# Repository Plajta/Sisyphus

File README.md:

# Sisyphus
This repository includes the hardware, firmware, chassis and documentation for our soundboard helping those who need it (or don't and want a thing that makes sounds).

Code for the firmware's web configurator (Lithos) can be found [here](https://github.com/Plajta/lithos).

## Key features
Built using open source software on widely documented hardware.

With RP2040 as it's beating heart and a nice crisp I2S DAC, it can (but probably won't be used to) do CD quality audio.

Built into a strudy, but slim and relatively lite 3D printed construction, held together by friction and screws for ease of repair and construction. (construction manual coming soon™)

## Directory structure
- [3D](3D/) - FreeCAD project, the [STLs](3D/STLs) subdirectory includes the exported files ready for 3D printing
- [PCBs](PCBs/) - Two KiCAD projects, one for Sisyphus's [mainboard](PCBs/sisyphus) and one for our own slim [RGB sensor module](PCBs/rgb_sensor)
- [src](src/) - The board's firmware, has it's own README, also usable on a Raspberry Pi Pico with a bit of configuration

## Licensing
All main directories have their own LICENSE files.

`3D` and `PCBs` are under CC-BY-SA. `src` is licensed under GPL3.
That means you can use the whole thing, or just a part of it in your commercial projects but must publically share your potential changes under the same license.

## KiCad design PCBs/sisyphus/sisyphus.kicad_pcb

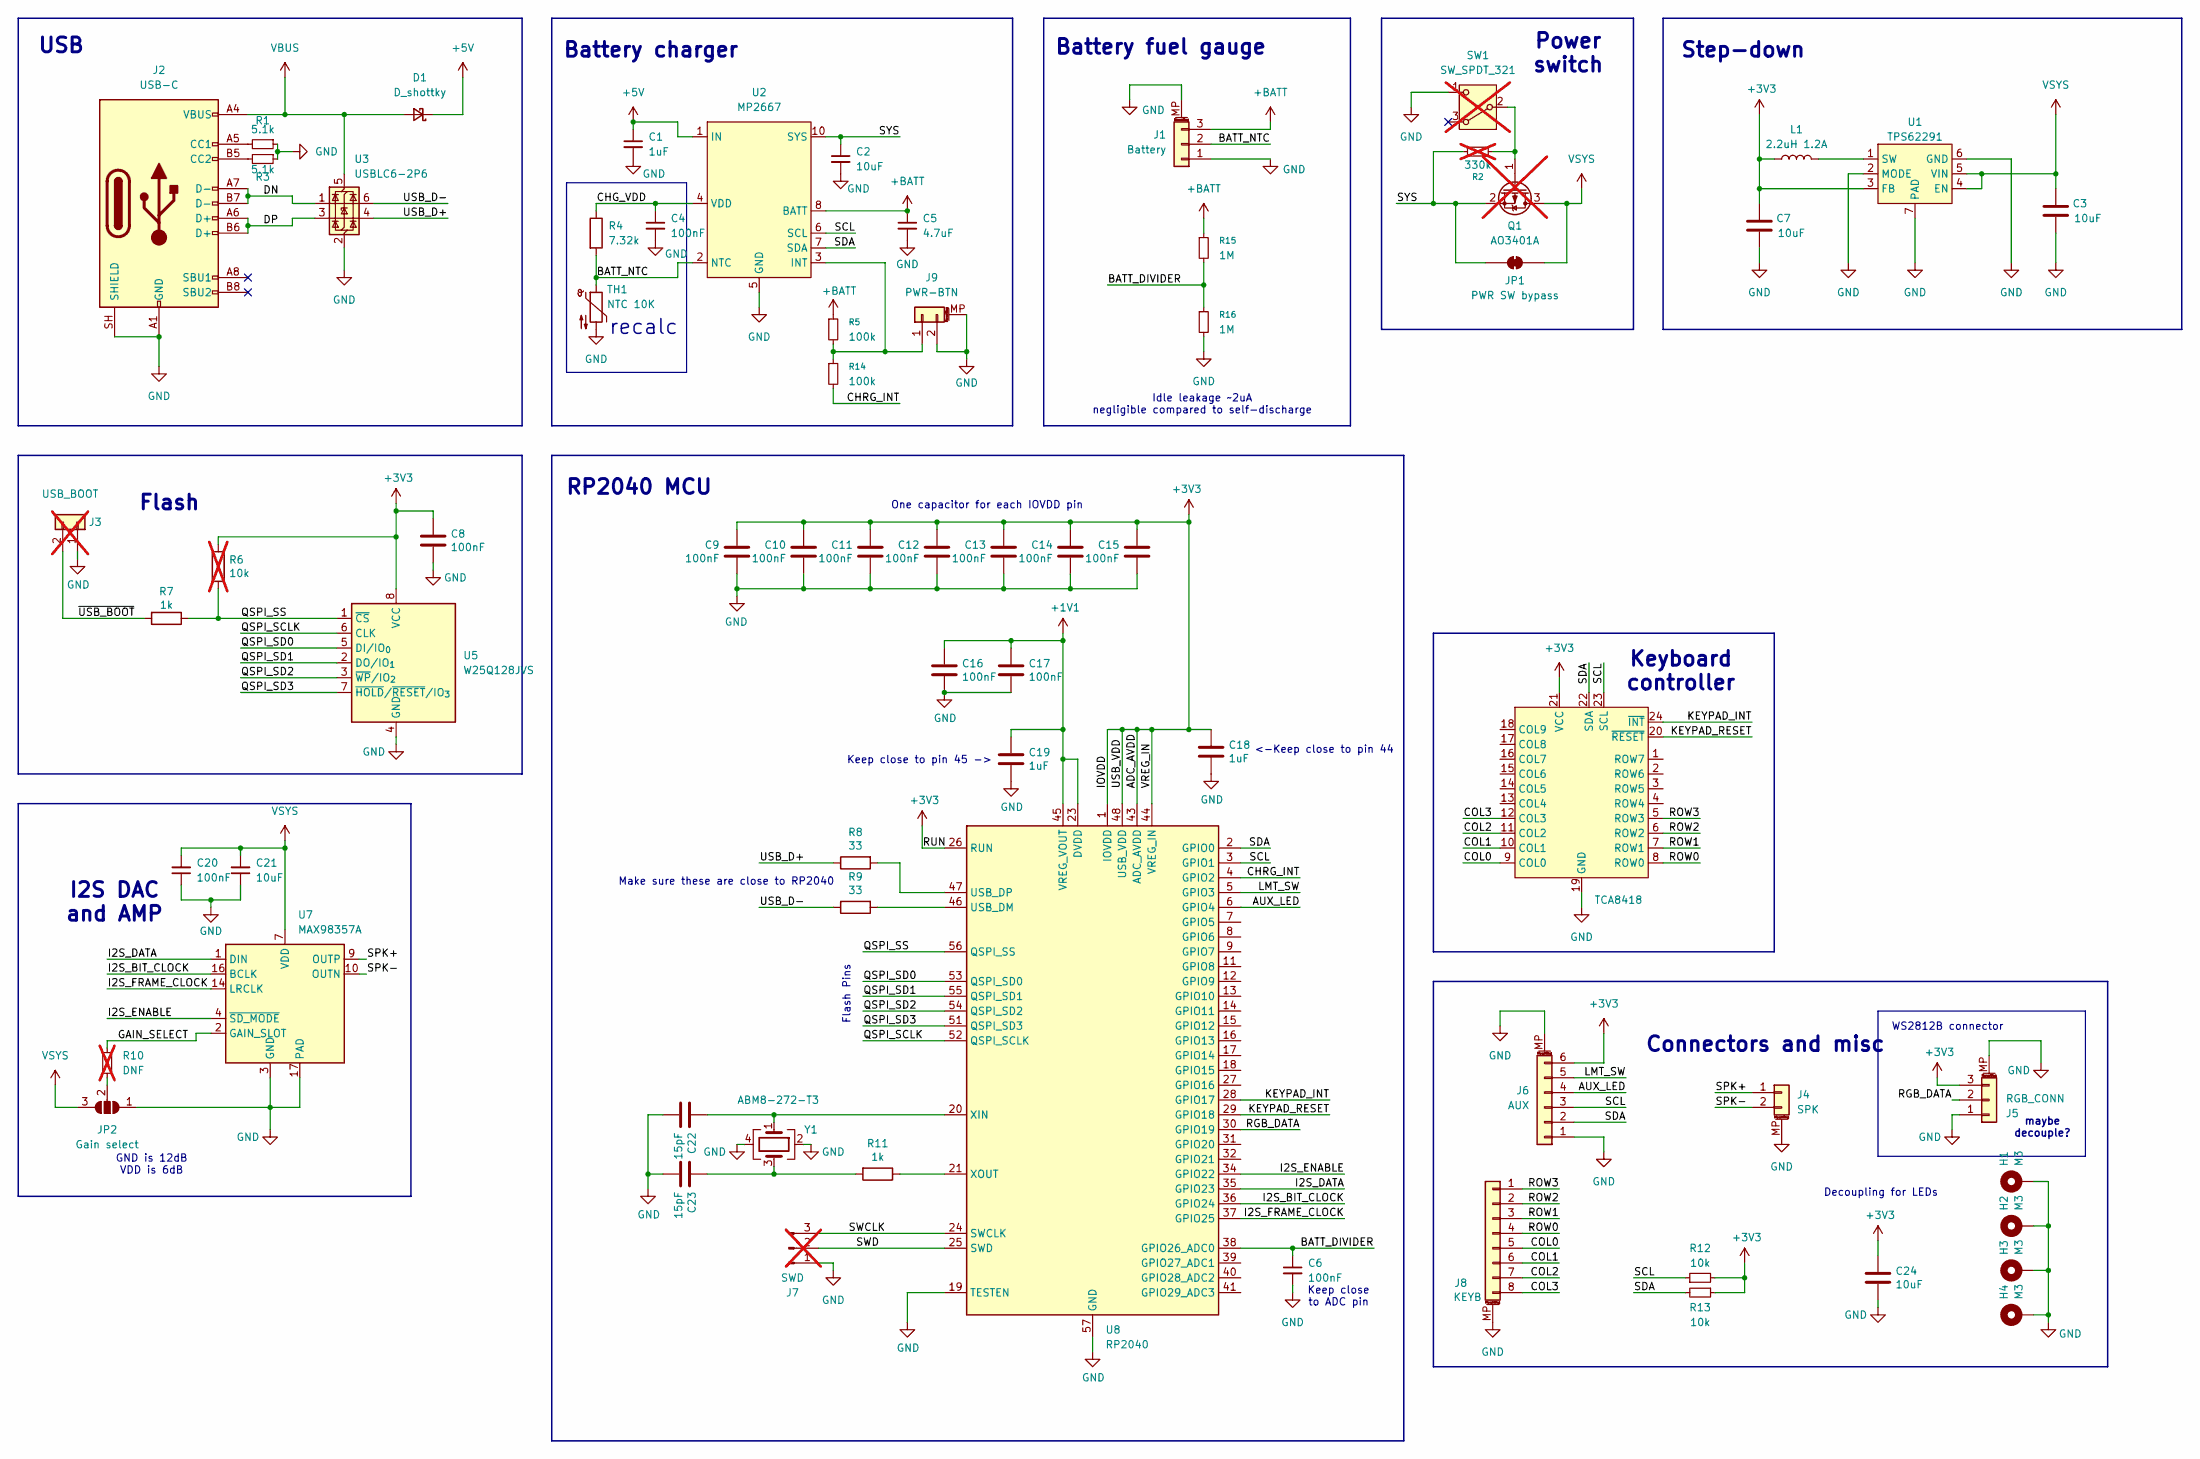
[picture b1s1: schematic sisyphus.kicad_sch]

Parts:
C1, C18, C19: 1uF; C_0402_1005Metric
C2, C3, C7, C21, C24: 10uF; C_0402_1005Metric
C4, C6, C8, C9, C10, C11, C12, C13, C14, C15, C16, C17, C20: 100nF; C_0402_1005Metric
C5: 4.7uF; C_0402_1005Metric
C22, C23: 15pF; C_0402_1005Metric
D1: D_shottky; D_SOD-123F; Mouser Part 863-MBR230LSFT1G
H1, H2, H3, H4: M3; MountingHole_3.2mm_M3_ISO7380_Pad
J1: Battery; JST_PH_S3B-PH-SM4-TB_1x03-1MP_P2.00mm_Horizontal; Mouser Part 306-S3BPHSM4TBLFSN
J2: USB-C; USB_C_Receptacle_GCT_USB4105-xx-A_16P_TopMnt_Horizontal; Mouser Part 640-USB4105-GF-A-120
J3: USB_BOOT; PinHeader_1x02_P1.00mm_Vertical; not fitted
J4: SPK; JST_PH_S2B-PH-SM4-TB_1x02-1MP_P2.00mm_Horizontal; Mouser Part 306-S2BPHSM4TBLFSN
J5: RGB_CONN; JST_PH_S3B-PH-SM4-TB_1x03-1MP_P2.00mm_Horizontal; Mouser Part 306-S3BPHSM4TBLFSN
J6: AUX; JST_PH_S6B-PH-SM4-TB_1x06-1MP_P2.00mm_Horizontal; Mouser Part 306-S6BPHSM4TBLFSN
J7: SWD; PinHeader_1x03_P2.54mm_Vertical; not fitted
J8: KEYB; JST_PH_S8B-PH-SM4-TB_1x08-1MP_P2.00mm_Horizontal; Mouser Part 306-S8BPHSM4TBLFSN
J9: PWR-BTN; JST_PH_S2B-PH-SM4-TB_1x02-1MP_P2.00mm_Horizontal; Mouser Part 306-S2BPHSM4TBLFSN
JP1: PWR SW bypass; SolderJumper-2_P1.3mm_Bridged2Bar_RoundedPad1.0x1.5mm
JP2: Gain select; SolderJumper-3_P1.3mm_Open_RoundedPad1.0x1.5mm
L1: 2.2uH 1.2A; L_0805_2012Metric
Q1: AO3401A; SOT-23; LCSC Part C347476; not fitted
R1, R3: 5.1k; R_0402_1005Metric
R2: 330k; R_0402_1005Metric; not fitted
R4: 7.32k; R_0402_1005Metric
R5, R14: 100k; R_0402_1005Metric
R6: 10k; R_0402_1005Metric; not fitted
R7, R11: 1k; R_0402_1005Metric
R8, R9: 33; R_0402_1005Metric
R10: DNF; R_0402_1005Metric; not fitted
R12, R13: 10k; R_0402_1005Metric
R15, R16: 1M; R_0402_1005Metric
SW1: SW_SPDT_321; PinHeader_1x03_P2.54mm_Vertical; not fitted
TH1: NTC 10K
U1: TPS62291; WSON-6-1EP_2x2mm_P0.65mm_EP1x1.6mm_ThermalVias; Mouser Part 595-TPS62291DRVR
U2: MP2667; MPS_MP2664_QFN-10_2x2mm_P0.5mm; Mouser Part 946-MP2667GG-0000-P
U3: USBLC6-2P6; SOT-666; Mouser Part 511-USBLC6-2P6
U5: W25Q128JVS; SOIC-8_5.3x5.3mm_P1.27mm
U6: TCA8418; WQFN-24-1EP_4x4mm_P0.5mm_EP2.45x2.45mm; Mouser Part 595-TCA8418RTWR
U7: MAX98357A; TQFN-16-1EP_3x3mm_P0.5mm_EP1.23x1.23mm; Mouser Part 700-MAX98357AETE+T
U8: RP2040; QFN-56-1EP_7x7mm_P0.4mm_EP3.2x3.2mm; Mouser Part 358-SC091413
Y1: ABM8-272-T3; Crystal_SMD_3225-4Pin_3.2x2.5mm; Mouser Part 815-ABM8-272-T3

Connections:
+1V1: C16.1, C17.1, C19.1, U8.23 (DVDD), U8.45 (VREG_VOUT), U8.50 (DVDD)
+3V3: C7.1, C8.1, C9.1, C10.1, C11.1, C12.1, C13.1, C14.1, C15.1, C18.1, C24.1, J5.3, J6.6, L1.1, R6.1, R12.2, R13.1, U1.3 (FB), U5.8 (VCC), U6.21 (VCC), U8.1 (IOVDD), U8.10 (IOVDD), U8.22 (IOVDD), U8.26 (RUN), U8.33 (IOVDD), U8.42 (IOVDD), U8.43 (ADC_AVDD), U8.44 (VREG_IN), U8.48 (USB_VDD), U8.49 (IOVDD)
+5V: C1.1, D1.1 (K), U2.1 (IN)
+BATT: C5.1, J1.3, R5.1, R15.1, U2.8 (BATT), U2.9 (BATT)
/AUX_LED: J6.4, U8.6 (GPIO4)
/BATT_DIVIDER: C6.1, R15.2, R16.1, U8.38 (GPIO26_ADC0)
/BATT_NTC: J1.2, R4.2, TH1.1, U2.2 (NTC)
/CHG_VDD: C4.1, R4.1, U2.4 (VDD)
/CHRG_INT: R14.2, U8.4 (GPIO2)
/COL0: J8.5, U6.9 (COL0)
/COL1: J8.6, U6.10 (COL1)
/COL2: J8.7, U6.11 (COL2)
/COL3: J8.8, U6.12 (COL3)
/DN: J2.A7 (D-), J2.B7 (D-), U3.1 (I/O1)
/DP: J2.A6 (D+), J2.B6 (D+), U3.3 (I/O2)
/GAIN_SELECT: R10.1, U7.2 (GAIN_SLOT)
/I2S_BIT_CLOCK: U7.16 (BCLK), U8.36 (GPIO24)
/I2S_DATA: U7.1 (DIN), U8.35 (GPIO23)
/I2S_ENABLE: U7.4 (~SD_MODE), U8.34 (GPIO22)
/I2S_FRAME_CLOCK: U7.14 (LRCLK), U8.37 (GPIO25)
/KEYPAD_INT: U6.24 (~INT), U8.28 (GPIO17)
/KEYPAD_RESET: U6.20 (~RESET), U8.29 (GPIO18)
/LMT_SW: J6.5, U8.5 (GPIO3)
/QSPI_SCLK: U5.6 (CLK), U8.52 (QSPI_SCLK)
/QSPI_SD0: U5.5 (DI/IO_{0}), U8.53 (QSPI_SD0)
/QSPI_SD1: U5.2 (DO/IO_{1}), U8.55 (QSPI_SD1)
/QSPI_SD2: U5.3 (~WP/IO_{2}), U8.54 (QSPI_SD2)
/QSPI_SD3: U5.7 (~HOLD/~RESET/IO_{3}), U8.51 (QSPI_SD3)
/QSPI_SS: R6.2, R7.1, U5.1 (~CS), U8.56 (QSPI_SS)
/RGB_DATA: J5.2, U8.30 (GPIO19)
/ROW0: J8.4, U6.8 (ROW0)
/ROW1: J8.3, U6.7 (ROW1)
/ROW2: J8.2, U6.6 (ROW2)
/ROW3: J8.1, U6.5 (ROW3)
/SCL: J6.3, R12.1, U2.6 (SCL), U6.23 (SCL), U8.3 (GPIO1)
/SDA: J6.2, R13.2, U2.7 (SDA), U6.22 (SDA), U8.2 (GPIO0)
/SPK+: J4.1, U7.9 (OUTP)
/SPK-: J4.2, U7.10 (OUTN)
/SWCLK: J7.3, U8.24 (SWCLK)
/SWD: J7.2, U8.25 (SWD)
/SYS: C2.1, JP1.2 (B), Q1.2 (S), R2.2, U2.10 (SYS)
/USB_D+: R8.1, U3.4 (I/O2)
/USB_D-: R9.1, U3.6 (I/O1)
/~USB_BOOT: J3.2, R7.2
GND: C1.2, C2.2, C3.2, C4.2, C5.2, C6.2, C7.2, C8.2, C9.2, C10.2, C11.2, C12.2, C13.2, C14.2, C15.2, C16.2, C17.2, C18.2, C19.2, C20.1, C21.1, C22.2, C23.2, C24.2, H1.1 (1_1), H2.1 (1_1), H3.1 (1_1), H4.1 (1_1), J1.1, J1.MP (MountPin), J2.A1 (GND), J2.A12 (GND), J2.B1 (GND), J2.B12 (GND), J2.SH (SHIELD), J3.1, J4.MP (MountPin), J5.1, J5.MP (MountPin), J6.1, J6.MP (MountPin), J7.1, J8.MP (MountPin), J9.2, J9.MP (MountPin), JP2.1 (A), R1.1, R3.1, R16.2, SW1.1 (C), TH1.2, U1.2 (MODE), U1.6 (GND), U1.7 (PAD), U2.5 (GND), U3.2 (GND), U5.4 (GND), U6.19 (GND), U6.25 (PAD), U7.3 (GND), U7.11 (GND), U7.15 (GND), U7.17 (PAD), U8.19 (TESTEN), U8.57 (GND), Y1.2, Y1.4
unnamed: C23.1, R11.2, Y1.3
unnamed: J2.A5 (CC1), R1.2
unnamed: J2.B5 (CC2), R3.2
unnamed: J9.1, R5.2, R14.1, U2.3 (INT)
unnamed: JP2.2 (C), R10.2
unnamed: Q1.1 (G), R2.1, SW1.2 (B)
unnamed: L1.2, U1.1 (SW)
unnamed: R9.2, U8.46 (USB_DM)
unnamed: R8.2, U8.47 (USB_DP)
unnamed: C22.1, U8.20 (XIN), Y1.1
unnamed: R11.1, U8.21 (XOUT)
VBUS: D1.2 (A), J2.A4 (VBUS), J2.A9 (VBUS), J2.B4 (VBUS), J2.B9 (VBUS), U3.5 (VBUS)
VSYS: C3.1, C20.2, C21.2, JP1.1 (A), JP2.3 (B), Q1.3 (D), U1.4 (EN), U1.5 (VIN), U7.7 (VDD), U7.8 (VDD)

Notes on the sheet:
Keep close to ADC pin
recalc
maybe decouple?
RP2040 MCU
USB
Battery charger
Keep close to pin 45 ->
GND is 12dB VDD is 6dB
I2S DAC and AMP
WS2812B connector
Keyboard controller
Decoupling for LEDs
Flash
Make sure these are close to RP2040
One capacitor for each IOVDD pin
Power switch
<-Keep close to pin 44
Flash Pins
Connectors and misc
Idle leakage ~2uA negligible compared to self-discharge
Step-down
Battery fuel gauge

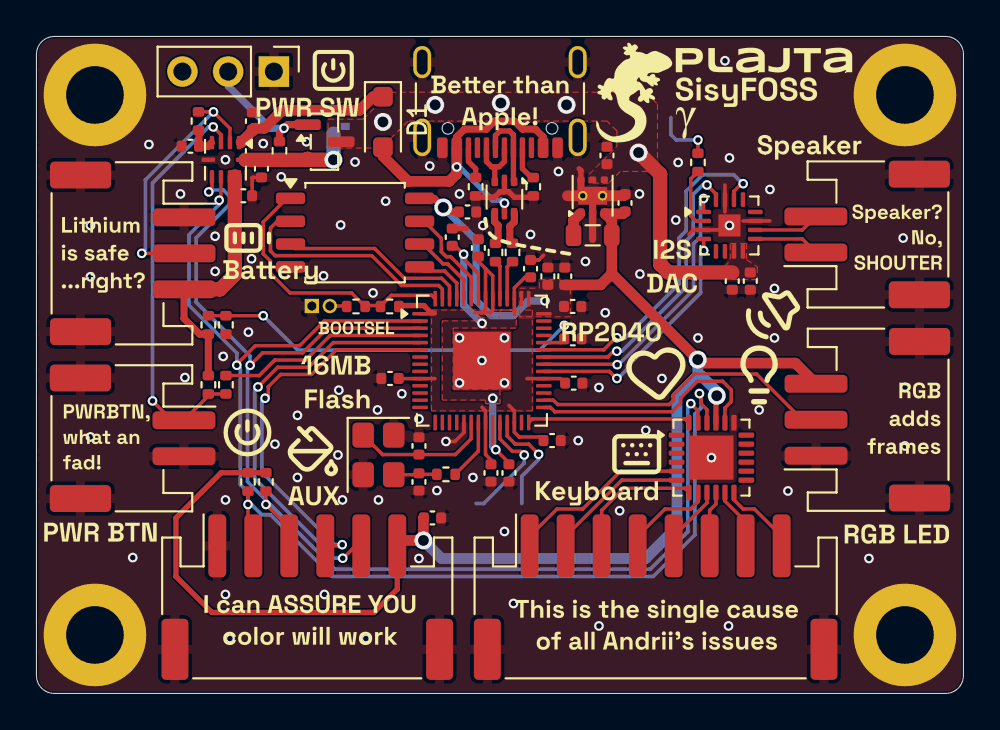
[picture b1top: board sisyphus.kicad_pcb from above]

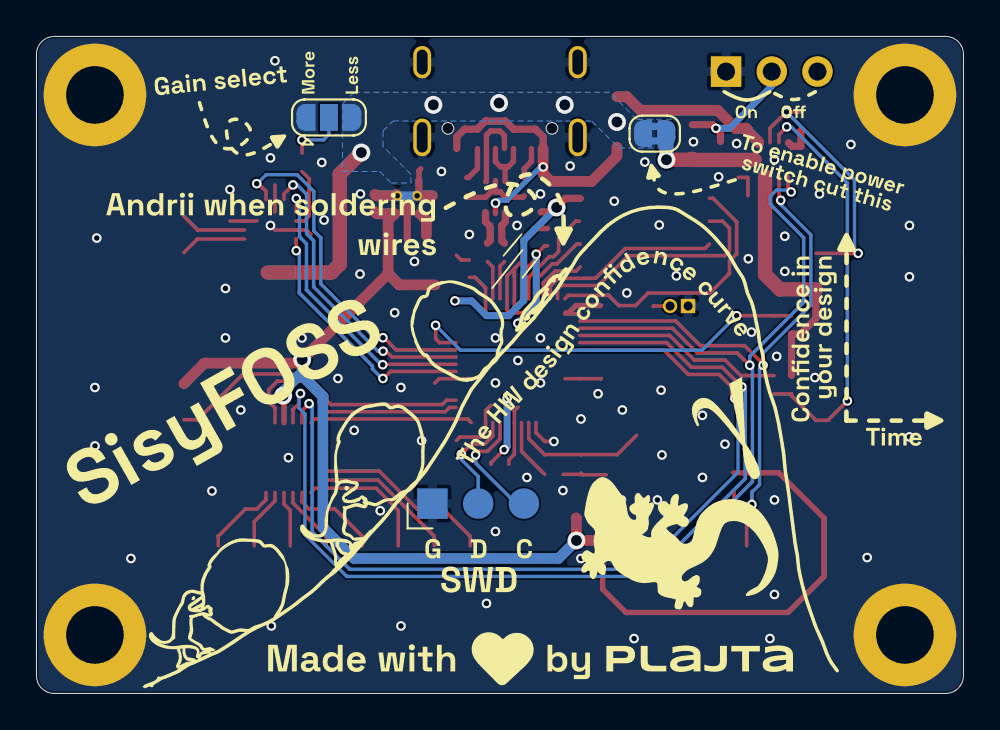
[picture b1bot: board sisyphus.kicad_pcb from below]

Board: 2 copper layers, 51.5 x 36.5 mm, 67 parts (3 on the bottom side), 58 nets.

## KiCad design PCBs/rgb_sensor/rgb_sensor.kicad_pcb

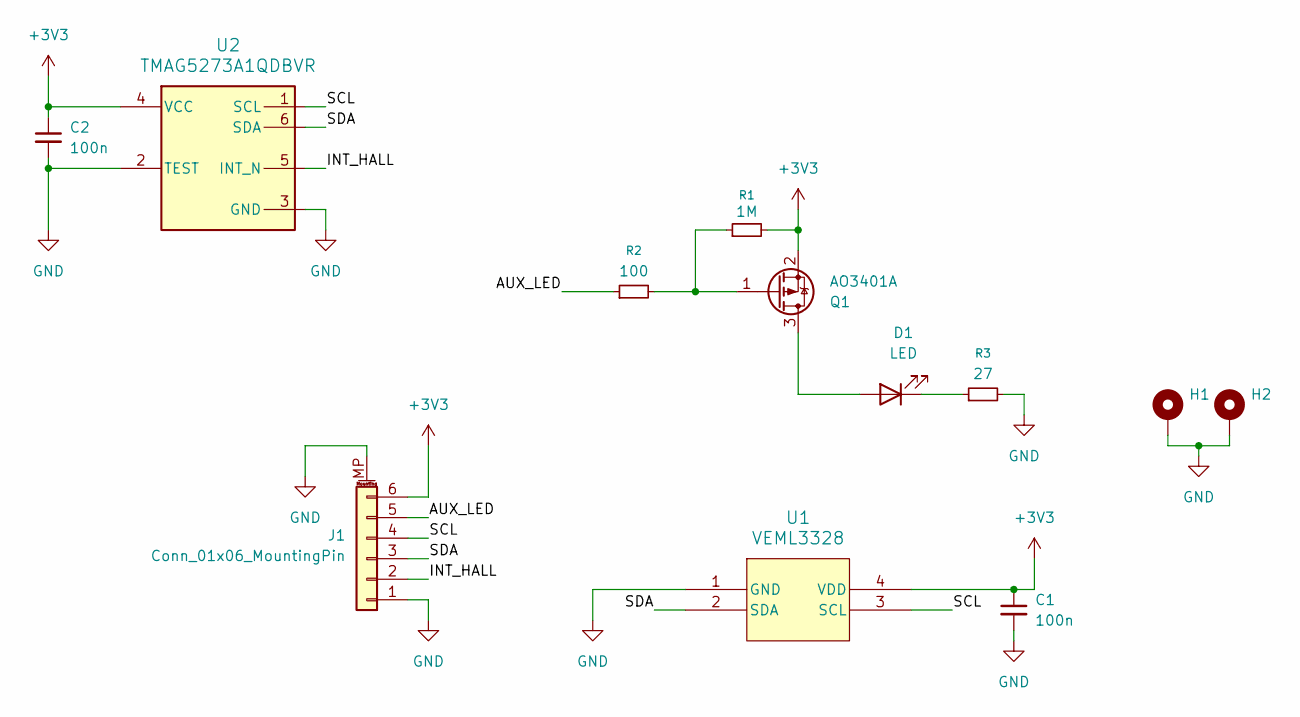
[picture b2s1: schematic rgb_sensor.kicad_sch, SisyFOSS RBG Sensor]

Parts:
C1, C2: 100n; C_0402_1005Metric
D1: LED; LED_0805_2012Metric
H1, H2: MountingHole_Pad; MountingHole_2.2mm_M2_Pad
J1: Conn_01x06_MountingPin; JST_SH_SM06B-SRSS-TB_1x06-1MP_P1.00mm_Horizontal
Q1: AO3401A; SOT-23
R1: 1M; R_0402_1005Metric
R2: 100; R_0402_1005Metric
R3: 27; R_0402_1005Metric
U1: VEML3328; SMD_L3328_VIS; Mouser Part 78-VEML3328; LCSC Part C509073
U2: TMAG5273A1QDBVR; DBV0006A-MFG; Mouser Part 595-TMAG5273A1QDBVR; LCSC Part C3716049

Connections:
+3V3: C1.1, C2.1, J1.6, Q1.2 (S), R1.2, U1.4 (VDD), U2.4 (VCC)
/AUX_LED: J1.5, R2.1
/INT_HALL: J1.2, U2.5 (INT_N)
/SCL: J1.4, U1.3 (SCL), U2.1 (SCL)
/SDA: J1.3, U1.2 (SDA), U2.6 (SDA)
GND: C1.2, C2.2, H1.1 (1_1), H2.1 (1_1), J1.1, J1.MP (MountPin), R3.2, U1.1 (GND), U2.2 (TEST), U2.3 (GND)
unnamed: D1.2 (A), Q1.3 (D)
unnamed: D1.1 (K), R3.1
unnamed: Q1.1 (G), R1.1, R2.2

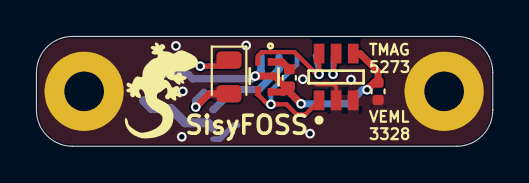
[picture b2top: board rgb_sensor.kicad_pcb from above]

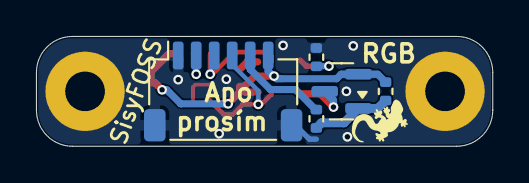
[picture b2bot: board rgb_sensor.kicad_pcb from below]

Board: 2 copper layers, 25.3 x 6.1 mm, 12 parts (5 on the bottom side), 9 nets.

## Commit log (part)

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2025-03-14 ahh piko
2025-03-14 web jede brrr
2025-03-14 velice official dashboard route
2025-03-14 uploaded modified APDS9960 code that is not working (plis helb)
2025-03-15 upravenej hlavni layout
2025-03-15 stranka na konfiguraci
2025-03-15 zobrazovat breadcrmb dynamicky pres navitem
2025-03-15 highlight veci v menu
2025-03-15 zakladni layout tlacitek
    zatim rohliky
2025-03-15 zobrazovat cursor pointer kdyz tlacitko
2025-03-15 velice scuffed modal system
2025-03-15 voice recorder
2025-03-15 shell dialogu na upravu tlacitka
2025-03-15 databaze databazuje
2025-03-15 zaklad pro handlovani souboru
2025-03-15 formwrapper a nejaky edit funkcionality
2025-03-15 nacitat tlacitka z db
2025-03-15 upravujeme nazvy tlacitek hezkym zpusobem
2025-03-15 WE CAN FINALLY SENS DA FOCKIN COLEURS
2025-03-15 nahravani obrazku a spravna velikost tlacitek
2025-03-15 responzivni uz je
2025-03-15 preahravani videa v kartach pro tlacitka
2025-03-15 podpora sheetu
2025-03-15 brat png jenom
2025-03-15 dialog funguje i s sheetem
2025-03-15 spravne brat a zobaovar breadrcumb & navitems
2025-03-15 prvni integrace zapisu a čtení sd karty
2025-03-15 jsem hloupy kluk
2025-03-15 Ehmm enohf for mee ahhhh
2025-03-15 ahh page gameplay
2025-03-15 list sheetu do menu
2025-03-15 fixed gitignore
2025-03-15 umime vytvaret x ruznejch konfiguraci
2025-03-15 pomoc prave jsem zanechal stopu na internetu (asi ne?)
2025-03-15 added new files
2025-03-15 Auto stash before merge of "main" and "origin/main"
2025-03-15 fixed class values + changed because andri forgot the schema
2025-03-15 zakladni velice scuffed generace pdf
2025-03-15 FOckun submodules
2025-03-15 generace naseho pdf sheetu
2025-03-15 copyright
2025-03-15 muck
2025-03-15 offsetovat pdf sheet
2025-03-15 udelat vohejbani
2025-03-15 čas na hranění deadlinu
2025-03-15 it workie finalli
2025-03-15 vopravenej grid kurva
2025-03-15 priprava na typy sheetu
2025-03-15 Full asembly
2025-03-15 remove readback
2025-03-15 FASTER
2025-03-15 changed out
2025-03-15 sd card integration
2025-03-16 sd card reading functions
2025-03-16 seriova komunikace a nahravani
2025-03-16 nom nom
2025-03-16 pres parametr generovast
2025-03-16 working file transfer wave stil dogshit
2025-03-16 generace templatu i pro ten pseudo device
2025-03-16 prejmenovat projekt
2025-03-16 podpora tvorby tabulek pro ft12
2025-03-16 spravna generace radku
2025-03-16 pryc navactions
    zatim se nepouzivajiu
2025-03-16 i file input
2025-03-16 Very ugly but unfortunately functional PoC of the code...
2025-03-31 Add battery testing battery charger implementation Also remove unncessary tracked files
2025-04-02 Update main PCB
2025-04-02 Update 3D model
2025-04-05 Created new method how to click on button
2025-04-06 Initial LittleFS import Added LittleFS git module as a library Cleaned up Added a custom memory map so LittleFS has it's own place in the flash
2025-04-06 Update CMakeLists.txt Enable memory usage printing from linker Rearange and add comments Change LITTLEFS parition size definition and add a check for size
2025-04-06 Improved button
2025-04-06 LittleFS support + cleanup + debug setup Add LittleFS support with a demo Cleanup Add a way to quickly turn debugging messages on and off
2025-04-09 Add prototype transfer protocol Protocol is still work in progress, i just wanted to write it down.
2025-04-14 prekopirovat web
2025-04-14 exportovat staticke html
2025-04-14 soubory uz nebudou potreba
2025-04-14 smazat a vypnout serverove casti
2025-04-14 stav managovat pres zustand
2025-04-14 renderovat spravne sidebar
2025-04-18 Add a basic structure for USB comms and button interrupt
2025-04-25 Make define not colide with an existing one
2025-04-25 Update WIP Protocol docs
2025-04-27 Huge firmare update
    Rewrite PROTOCOL.md - with help from an LLM, MAY CONTAIN ERRORS
    Add both sides of the protocol a device side in the firmware and a
    reference python shell that can be used to test it
    Few changes to file layout
    Add a way to build and flash using `make flash`
2025-04-27 Update reference python client
    Make speed calculation more readable
    Make tab completion better
    Fix bug in `rm` command
2025-04-27 Add audio playback from LFS
    The sample header is no longer needed
2025-04-27 Remove auto-processing
    It is not longer needed as firmware can play WAV's from it's filesystem
2025-04-27 Separate protocol.py
    It can now be used in any script
    client.py now uses it as a backend for communication
    Add __pycache__ to .gitignore
2025-04-27 Add play command
    Move audio to a separate directory
    Remove guards and replace for `#pragma once`
2025-04-27 Started work on 3d model also designed better spring
2025-04-27 Make LittleFS cache size bigger
    Now 16x the size!
2025-04-27 Add an info command
    Add a lot of info to the binary
2025-04-27 Add a audio converter script
2025-04-28 zaklad pipeliny na nahravani do github pages
2025-04-28 zakladni nacitani konfigurace ze zipu
2025-04-28 nadpisy do breadcrumbu
2025-04-28 ghost varianta inputu
2025-04-28 Update firmware workflow
2025-04-28 Replace pico_stdio_usb with raw TinyUSB
    It wasn't as bad as i thought...
    Add reset command to protocol because we lost the native picotool one
    Add a script to automatically find the device and reset it
2025-04-28 Make reference protocol client autosearch
2025-04-28 Add autofind to convert.py
2025-05-04 Rename client.py to shell.py
2025-05-05 Update protocol docs
2025-05-05 Remove unnecessary include
2025-05-05 Update connection exception type
2025-05-05 Make convert.py independent of `rich`
2025-05-05 Update workflow to include Eternity
2025-05-05 Make device side protocol reflect the other changes
2025-05-06 Add a static protocol indicator to `info`
    Update eternity submodule commit
    Update according docs
    Protocol version was NOT raised because of the early development stage
2025-05-08 zaklad seriove komunikace
2025-05-14 Fix critical PCB errors
2025-05-14 Add some ✨flair✨ to the PCB
2025-05-16 Add power switch
    Minor changes
2025-05-18 Improved spring, now loking like its acting as clicking, started work on scalar buttons
2025-05-18 Some schematic readability improved. Minor changes in PCB
2025-05-18 Update things for that rendering F L A R E
2025-05-31 Add the first actually ordered version of the PCB
2025-06-02 Add the RGB sensor module
    Remove sisyphus-matrix, it was just for testing
    Move symbol library up a directory so it can be shared
2025-06-03 Update RGB sensor
2025-06-03 Update some details about connectors
2025-06-03 Setup for SisyFOSS β PCB
    Add a board header
    Add support for defining LFS size in board header
2025-06-11 Add I2S pins to boards
    Add default
2025-06-11 Add SisyFOSS Beta board's specific builds to actions
2025-06-11 Fix typo
2025-06-12 Update board config with all pins
2025-06-12 Add keyboard driver
    Still doesn't decode keys to audio filenames but it is THERE
2025-06-17 Fixed building, added requirements for python scripts, 3D update
2025-06-21 Started work on charger
2025-06-21 Fixed clangd conf
2025-06-21 Fix 3D model path
    Add it to git and add attribution
2025-06-22 Just drop of semi tested 3D model
2025-06-22 Update RGB sensor PCB
    Just a small tweak for a manufacturing
2025-07-06 3D update
2025-07-23 Add color sensor driver + color LUT + misc
    Generally add a lot of color related things - things for other drivers
    Add a command to read the color sensor to firmware and to python scripts
    Add a python script to visualize data from sensor
    Add a small amount of error handling, i'll rewrite it later
    Fix a few things
2025-07-23 Clean up protocol.c
2025-07-23 Remove an unnecessary argument that didn't break it???? What??
2025-09-13 Update Eternity
    Fixes a very stupid build error
2025-09-13 Simplify error catching
    Preparation for full error catching coverage
2025-09-13 Move RPi's licensing from main.c to the relevant file
2025-09-13 Add a place for debug text on connect
2025-09-13 Add a Sisyphus debug flag to the info command
    IF IT IS NOT DO NOT SHIP THAT DEVICE OR FIRWMARE
    Also added warnings that say the same
2025-09-14 Make `error` a library and use it in color thingies
2025-09-14 Add playback based on button index and color code
    And it's done! This is basically all the functionality we wanted to achieve.
    There is still stuff to do. I'll start with the docs, but the code still has it's weakspots.
2025-09-14 Update READMEs, add docs, fix typos
2025-09-18 Remove unused variable
2025-09-18 Make Actions only build on PRs and `main` pushes
2025-09-20 Fixed error handling on color init
    This caused the LED to never get turned off
2025-09-20 Add a check for unscanned or invalid color_code
2025-09-20 Untangle IRQ mess
    This one was a DOOZY, but it works now and it's sooooo nice
2025-09-20 Add Lid detection (#1)
    * Preparation for lid detection
    * Add a check for unscanned or invalid color_code
    * Untangle IRQ mess
    This one was a DOOZY, but it works now and it's sooooo nice
2025-09-21 Fix wrongly broken behavior
    Audio just restarted when the button got clicked while playing, this was broken with Lid detection's rewrite of wakeup.
    Before this commit the audio stops, pressing a button behaves like a stop button, we don't want that tho.
2025-09-21 3D improvements: Almost final version
2025-09-21 Remove unused includes, shut `clangd` up
2025-09-21 Forgor to shut `clangd` here...
2025-09-21 Chat GPT can code even simple union 💀
2025-09-21 As I got, I also can't write simple union 💀
2025-09-22 Remove unnecesary PDF from the PCBs folder
2025-09-24 3D: Final version? 🤔
2025-10-10 Some minor 3D updates
2025-10-26 Add a PIO driver for RGB LED
    This is meant to serve as a status LED for the user and for debugging.
    This is the first commit of a few working on the bringup of RGB status LEDs.
2025-10-26 Redo lightshow
2025-10-26 Fix forgotten return
2025-10-26 Add optional color representation to LUT
    Also integrate it to the lightshow code
2025-10-26 Fix LUT parser pointer math
    It really was that simple
2025-10-31 New lightshow
    Now it blinks only when color is detected
2025-11-03 Remove old web configurator files
    Moved to https://github.com/Plajta/lithos
2025-12-29 Lower PMIC currents on SisyFOSS Beta
    A 1A charging current could TECHNICALLY be too much for some USB ports, this could also be a cause of some of the failures we experienced.
2025-12-29 Add an ARGB LED indicator (#2)
    * Add a PIO driver for RGB LED
    This is meant to serve as a status LED for the user and for debugging.
    * Add a simple prototype of a bootup sequence
    * Add optional color representation to LUT
    Also integrate it to the lightshow code
    * Fix LUT parser pointer math
2025-12-29 Update README.md
    Update a reference to Lithos
2025-12-29 Add a calibrator script
    The script prompts the user to insert the calibration papers and automatically sends the new LUT to the device after it's done. It has some predefined colors but new ones are easy to add.
    Maybe i should also add a calibration paper generator, but that's for another day.
2025-12-29 Change sample freq to 22000
    We really do not need CD quality LMAO. The small speakers don't stand a chance at reproducing that.
2025-12-29 Change files to `<color>_<row>_<column>.wav`
2025-12-29 Update reference audio conversion script
    Change frequency to 22000
2025-12-29 Update maximum color distance
    Made the distance a little bit tighter, needs testing but seems to work nice and eliminates false positives
2026-01-01 Add volume control
    Also add a variable to check if the lid is open or closed and used it in one place where it doesn't even need to be
    It might be a little bit fishy UX-wise tho, top left button (1) is volume - and the one to the right (2) is +
2026-01-10 Add white to calibrator
    Add white as a new predefined color
2026-02-11 Update README
    Maybe good now???
2026-02-17 Rewrite CMakeLists so boards more boards actually work
2026-03-20 Make audio *actually* play at 22kHz
    Whoops, it was 22100 before, it's not THAT big of a deal, but still
